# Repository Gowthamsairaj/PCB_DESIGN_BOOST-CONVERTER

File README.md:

⚡ DC-DC Boost Converter – PCB Design

Design and implementation of a step-up (boost) converter using professional PCB design practices.
This project demonstrates schematic capture, component selection, PCB layout, and power routing using KiCad.

📌 Project Overview

A boost converter increases a lower DC input voltage to a higher DC output voltage.
Such converters are widely used in:

Battery-powered systems

Embedded devices

Renewable energy systems

Industrial electronics

This repository contains the complete design files required for simulation, modification, and fabrication.

🎯 Objectives

✔ Design a stable DC-DC step-up converter
✔ Implement proper feedback and filtering
✔ Create manufacturable PCB layout
✔ Follow good grounding and high-current routing practice
✔ Prepare files for fabrication

🧠 Working Principle

The converter operates by switching an inductor using a transistor/MOSFET.

When the switch is ON → energy stored in inductor

When the switch is OFF → energy released to output

Capacitor smooths the voltage

Diode controls current direction

🛠 Design Tool

KiCad (Open-source EDA)

📂 Repository Contents

Boost.kicad_sch → Schematic design

Boost.kicad_pcb → PCB layout

pcb/ → PCB related files

Boost-backups/ → Backup & autosave files

Project configuration files

🔌 Key Components Used

Inductor

Switching device (MOSFET / transistor)

Diode

Output capacitor

Feedback resistors

📐 PCB Design Considerations

✔ Wide traces for high current paths
✔ Short loop area for switching section
✔ Proper grounding
✔ Noise reduction
✔ Component placement for thermal safety

🚀 Skills Demonstrated

Power electronics basics

Schematic design

PCB routing

Footprint association

Design rule awareness

Hardware development workflow

📈 Future Improvements

Add simulation results

Efficiency measurement

Thermal analysis

EMI optimization

Closed loop control using microcontroller

🎓 Academic / Learning Value

This project strengthens understanding of:

DC-DC converter operation

Switching behavior

Layout impact on performance

Real-world hardware design challenges

🤝 Contributions

Ideas, improvements, and layout optimization suggestions are welcome.

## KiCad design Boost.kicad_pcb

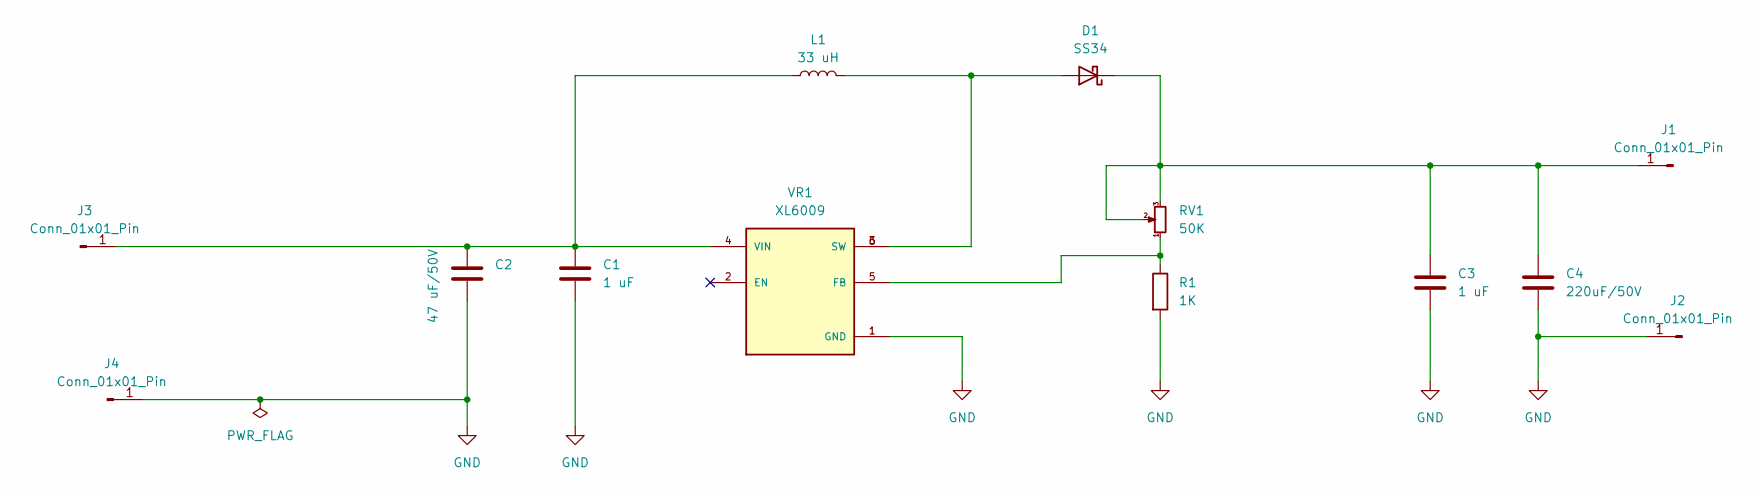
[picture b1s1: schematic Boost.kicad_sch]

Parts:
C1, C3: 1 uF; C_Radial_D5.0mm_H5.0mm_P2.00mm
C2: 47 uF/50V; C_Radial_D6.3mm_H5.0mm_P2.50mm
C4: 220uF/50V; C_Radial_D10.0mm_H12.5mm_P5.00mm
D1: SS34; D_SMA
J1, J2, J3, J4: Conn_01x01_Pin; PinHeader_1x01_P1.00mm_Horizontal
L1: 33 uH; L_Radial_D10.0mm_P5.00mm_Fastron_07M
R1: 1K; R_Axial_DIN0204_L3.6mm_D1.6mm_P1.90mm_Vertical
RV1: 50K; Potentiometer_Bourns_3386C_Horizontal
VR1: XL6009; DPAK170P1435X465-6N; PARTREV 1.1

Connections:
GND: C1.2, C2.2, C3.2, C4.2, J2.1, J4.1, R1.2, VR1.1 (GND)
unnamed: D1.2 (A), L1.2, VR1.3 (SW), VR1.6 (SW)
unnamed: C3.1, C4.1, D1.1 (K), J1.1, RV1.2, RV1.3
unnamed: C1.1, C2.1, J3.1, L1.1, VR1.4 (VIN)
unnamed: R1.1, RV1.1, VR1.5 (FB)

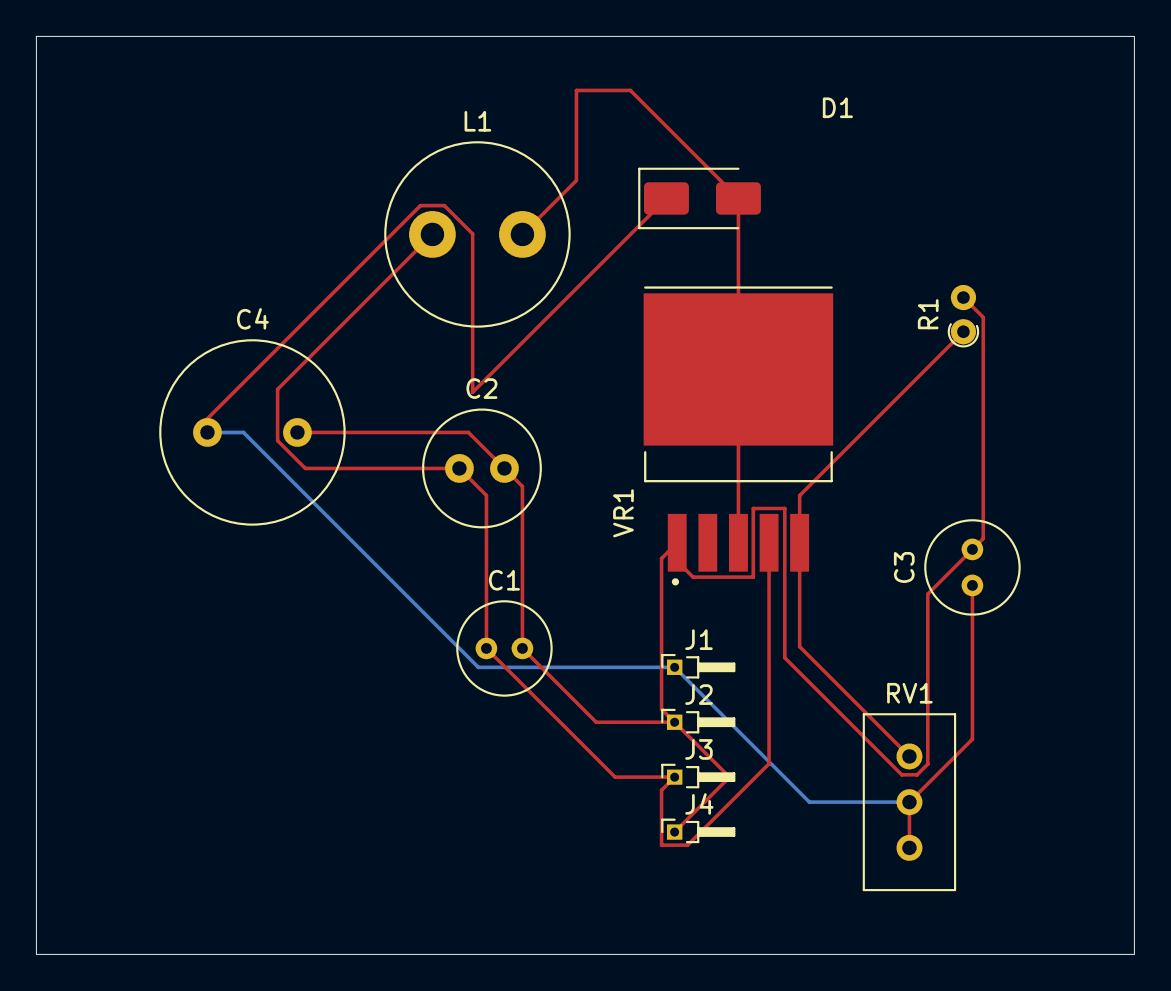
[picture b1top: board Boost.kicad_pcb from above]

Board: 2 copper layers, 61.0 x 51.0 mm, 13 parts (0 on the bottom side), 5 nets.

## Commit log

2025-03-21 BOOST CONVERTER
2026-02-08 Add README for DC-DC Boost Converter project
    Added comprehensive documentation for the DC-DC Boost Converter project, including objectives, working principles, design considerations, and future improvements.
